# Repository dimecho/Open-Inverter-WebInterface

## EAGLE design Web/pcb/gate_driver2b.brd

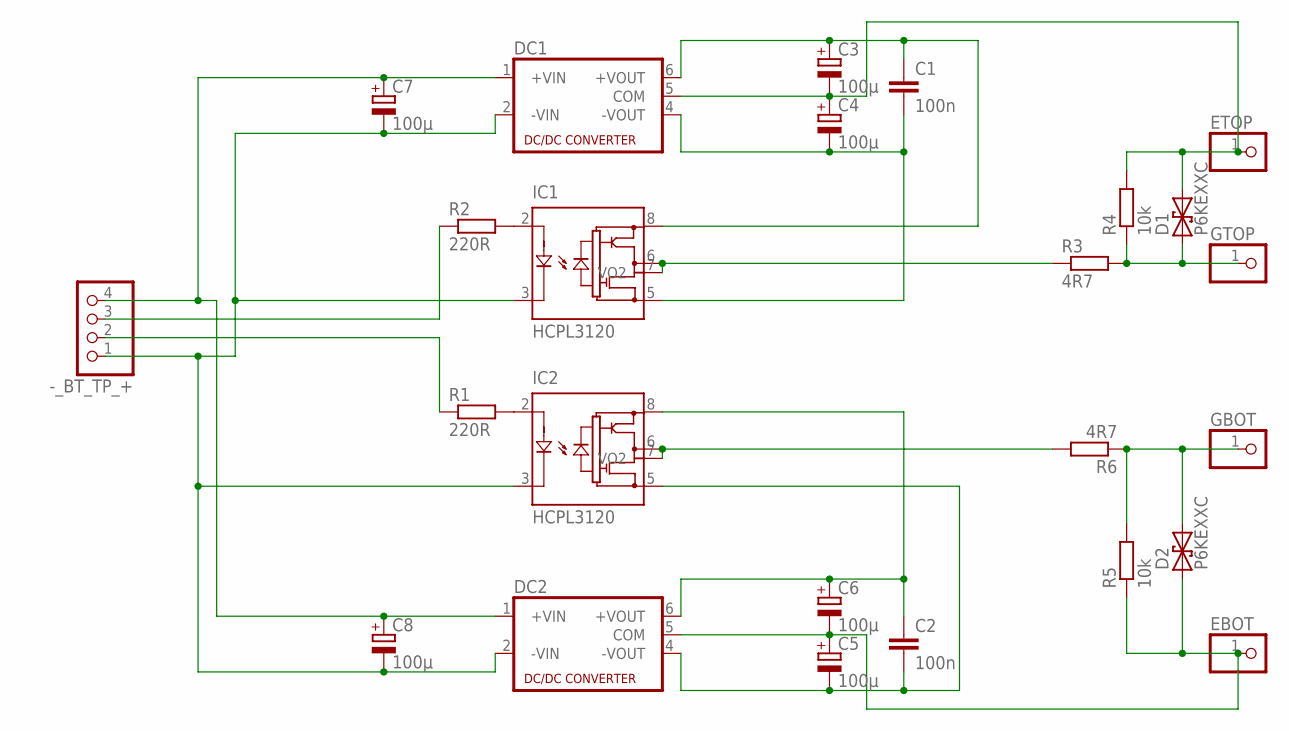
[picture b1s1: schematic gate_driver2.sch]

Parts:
-_BT_TP_+: PINHD-1X4; 1X04
C1, C2: 100n; C050-025X075
C3, C4, C5, C6: 100µ; E2,5-6E
C7, C8: 100µ; E2,5-5
D1, D2: P6KEXXC; CB417-15
DC1, DC2: NMA
EBOT: PINHD-1X1; 1X01
ETOP: PINHD-1X1; 1X01
GBOT: PINHD-1X1; 1X01
GTOP: PINHD-1X1; 1X01
IC1, IC2: HCPL3120; DIL08
R1, R2: 220R; 0207/10
R3, R6: 4R7; 0309/12
R4, R5: 10k; 0207/10

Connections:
EBOT: C5.+, C6.-, D2.A (1), DC2.5 (COM), EBOT.1, R5.1
ETOP: C3.-, C4.+, D1.C (2), DC1.5 (COM), ETOP.1, R4.2
GBOT: D2.C (2), GBOT.1, R5.2, R6.1
GND: -_BT_TP_+.1, C7.-, C8.-, DC1.2 (-VIN), DC2.2 (-VIN), IC1.3 (CATHODE), IC2.3 (CATHODE)
GTOP: D1.A (1), GTOP.1, R3.2, R4.1
unnamed: IC2.2 (ANODE), R1.2
unnamed: IC1.2 (ANODE), R2.2
unnamed: C1.2, C4.-, DC1.4 (-VOUT), IC1.5 (VEE)
unnamed: C1.1, C3.+, DC1.6 (+VOUT), IC1.8 (VCC)
unnamed: C2.1, C6.+, DC2.6 (+VOUT), IC2.8 (VCC)
unnamed: C2.2, C5.-, DC2.4 (-VOUT), IC2.5 (VEE)
unnamed: IC1.6 (VO), IC1.7 (VO2), R3.1
unnamed: IC2.6 (VO), IC2.7 (VO2), R6.2
unnamed: -_BT_TP_+.4, C7.+, C8.+, DC1.1 (+VIN), DC2.1 (+VIN)
unnamed: -_BT_TP_+.3, R2.1
unnamed: -_BT_TP_+.2, R1.1

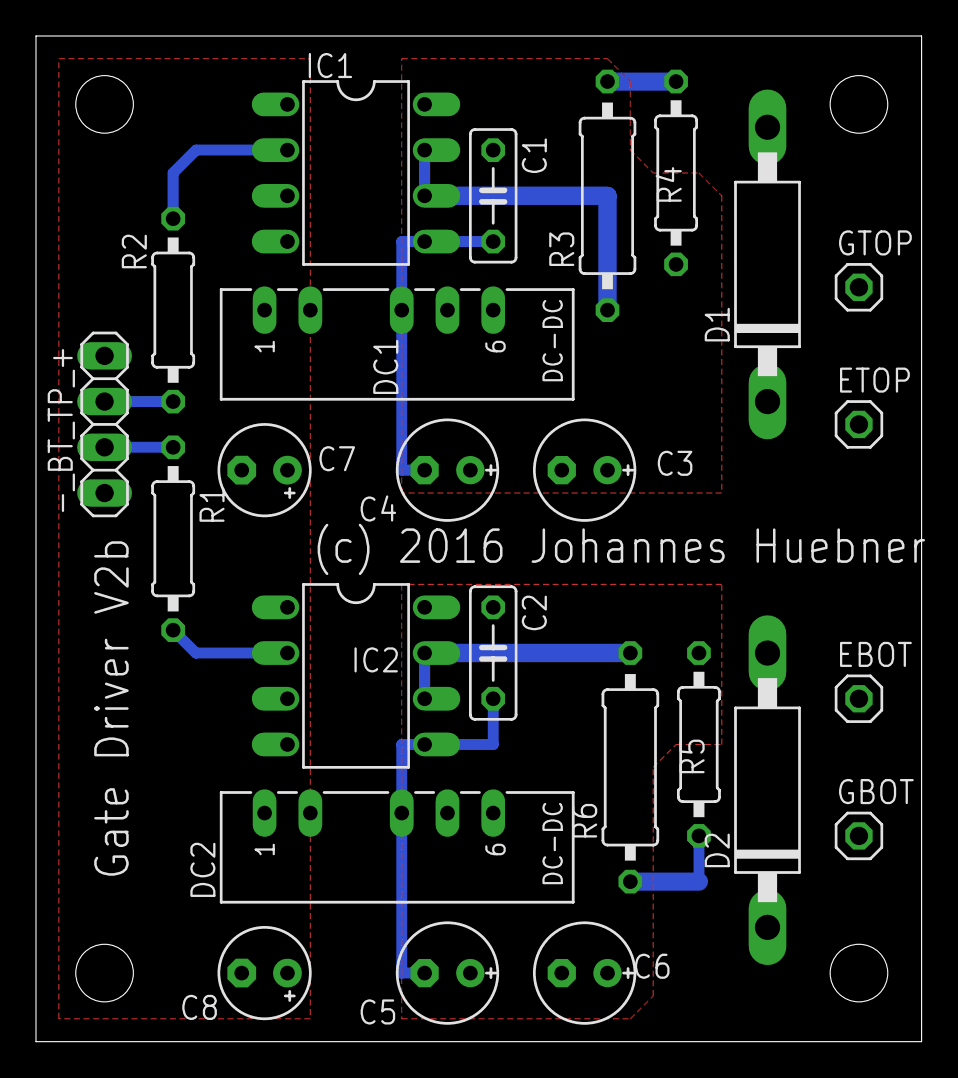
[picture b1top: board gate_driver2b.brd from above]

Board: 2 copper layers, 49.2 x 55.9 mm, 25 parts (0 on the bottom side), 16 nets.

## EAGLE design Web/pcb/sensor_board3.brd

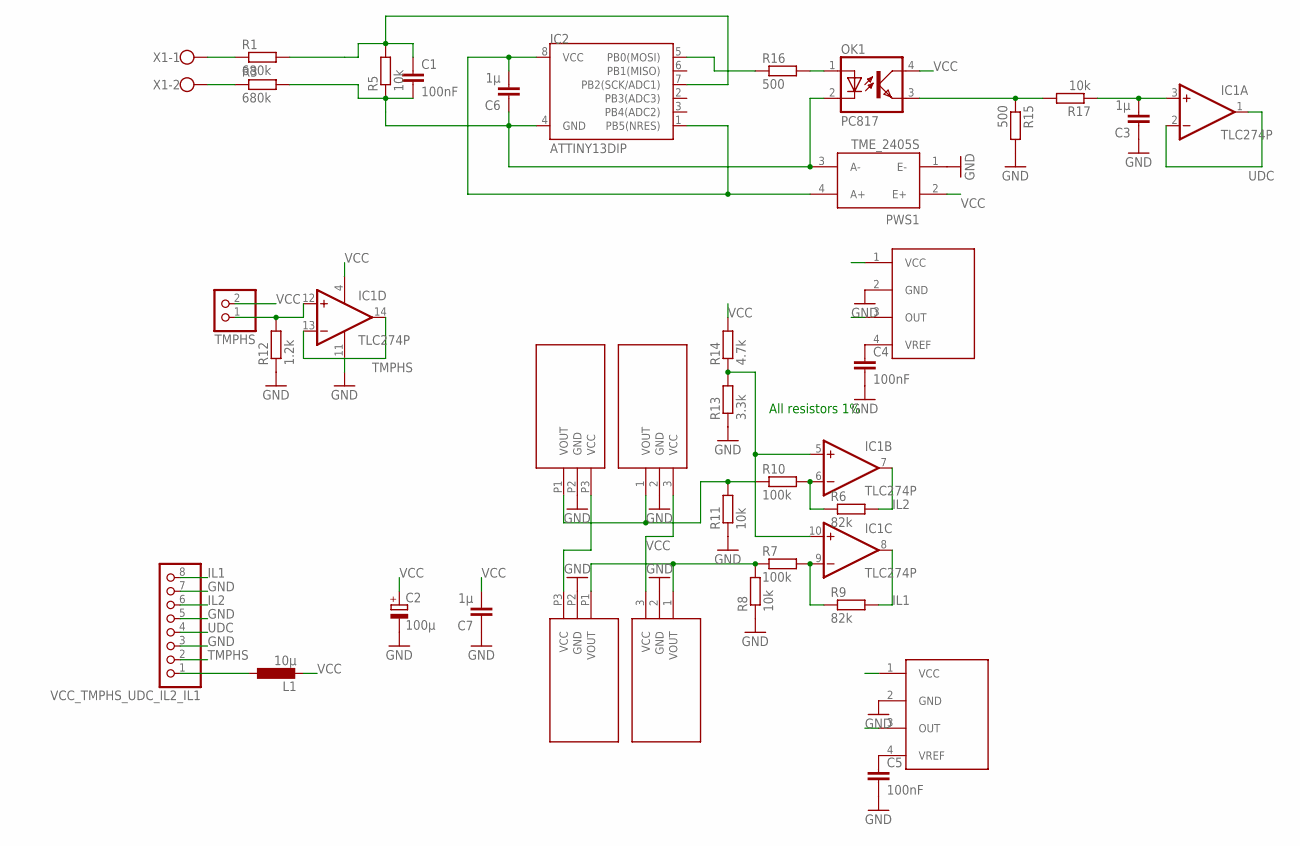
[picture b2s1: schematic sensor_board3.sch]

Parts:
C1, C4, C5: 100nF; C025-024X044
C2: 100µ; E2,5-6E
C3, C6, C7: 1µ; C025-024X044
IC1: TLC274P; DIL14
IC2: ATTINY13DIP; DIP08
L1: 10µ; 0207/12
OK1: PC817; DIL04
PWS1: TME_2405S; TMEXXXXS
R1, R3: 680k; 0207/10
R5, R8, R11, R17: 10k; 0207/10
R6, R9: 82k; 0207/10
R7, R10: 100k; 0207/10
R12: 1.2k; 0207/10
R13: 3.3k; 0207/10
R14: 4.7k; 0207/10
R15, R16: 500; 0207/10
TMPHS: PINHD-1X2; 1X02
U$1, U$2: TAMURA_L01Z_S05
U$3, U$4: HTFS
U$5, U$6: TAMURA_L06P_S05L06P; TAMURA_L06P_S05
VCC_TMPHS_UDC_IL2_IL1: PINHD-1X8; 1X08
X1: W237-102

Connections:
GND: C2.-, C3.1, C4.2, C5.2, C7.1, IC1.11 (V-), PWS1.1 (E-), R8.1, R11.1, R12.1, R13.1, R15.2, U$1.2 (GND), U$2.2 (GND), U$3.2 (GND), U$4.2 (GND), U$5.P2 (GND), U$6.P2 (GND), VCC_TMPHS_UDC_IL2_IL1.3, VCC_TMPHS_UDC_IL2_IL1.5, VCC_TMPHS_UDC_IL2_IL1.7
GND2: C1.2, C6.1, IC2.4 (GND), OK1.2 (C), PWS1.3 (A-), R3.2, R5.1
IL1: IC1.8 (OUT), R9.2, VCC_TMPHS_UDC_IL2_IL1.8
IL2: IC1.7 (OUT), R6.2, VCC_TMPHS_UDC_IL2_IL1.6
unnamed: IC1.5 (+IN), IC1.10 (+IN), R13.2, R14.1
unnamed: C1.1, IC2.7 (PB2(SCK/ADC1)), R1.2, R5.2
unnamed: R1.1, X1.1
unnamed: R3.1, X1.2
unnamed: L1.1, VCC_TMPHS_UDC_IL2_IL1.1
unnamed: IC1.9 (-IN), R7.2, R9.1
unnamed: IC1.6 (-IN), R6.1, R10.2
unnamed: OK1.3 (EMIT), R15.1, R17.2
unnamed: C4.1, U$3.4 (VREF)
unnamed: C5.1, U$4.4 (VREF)
unnamed: IC1.12 (+IN), R12.2, TMPHS.1
unnamed: OK1.1 (A), R16.2
unnamed: IC2.5 (PB0(MOSI)), R16.1
unnamed: C3.2, IC1.3 (+IN), R17.1
TMPHS: IC1.13 (-IN), IC1.14 (OUT), VCC_TMPHS_UDC_IL2_IL1.2
UDC: IC1.1 (OUT), IC1.2 (-IN), VCC_TMPHS_UDC_IL2_IL1.4
VCC: C2.+, C7.2, IC1.4 (V+), L1.2, OK1.4 (COL), PWS1.2 (E+), R14.2, TMPHS.2, U$1.3 (VCC), U$2.3 (VCC), U$3.1 (VCC), U$4.1 (VCC), U$5.P3 (VCC), U$6.P3 (VCC)
VCC2: C6.2, IC2.1 (PB5(NRES)), IC2.8 (VCC), PWS1.4 (A+)
VOUT1: R7.1, R8.2, U$2.1 (VOUT), U$4.3 (OUT), U$6.P1 (VOUT)
VOUT2: R10.1, R11.2, U$1.1 (VOUT), U$3.3 (OUT), U$5.P1 (VOUT)

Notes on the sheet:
All resistors 1%

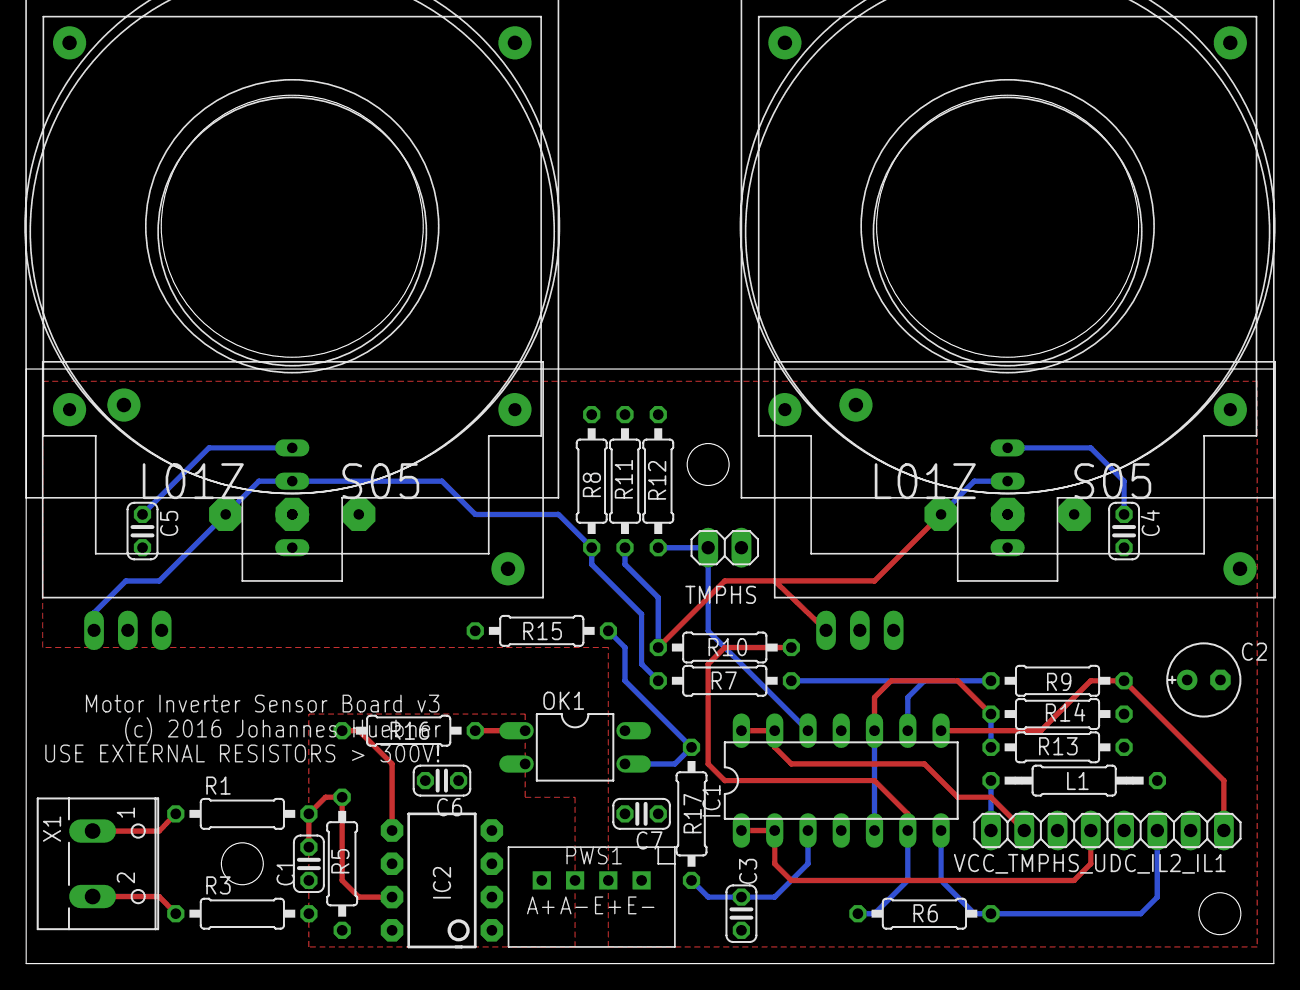
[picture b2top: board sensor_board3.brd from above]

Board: 2 copper layers, 95.2 x 45.4 mm, 36 parts (0 on the bottom side), 24 nets.

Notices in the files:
Web/pcb/gate_driver2b.brd:
(c) 2016 Johannes Huebner
parts and their libraries:
SparkFun-DigitalIC: Licensing: CC v3.0 Share-Alike You are welcome to use this library for commercial purposes.
